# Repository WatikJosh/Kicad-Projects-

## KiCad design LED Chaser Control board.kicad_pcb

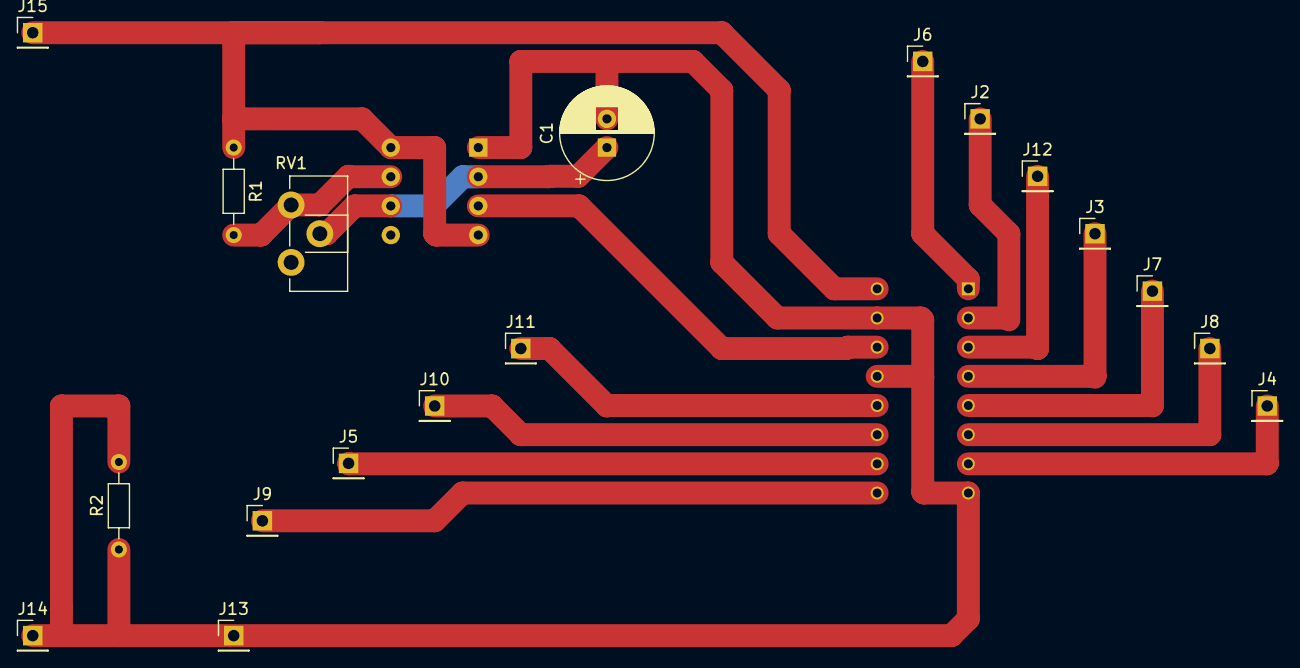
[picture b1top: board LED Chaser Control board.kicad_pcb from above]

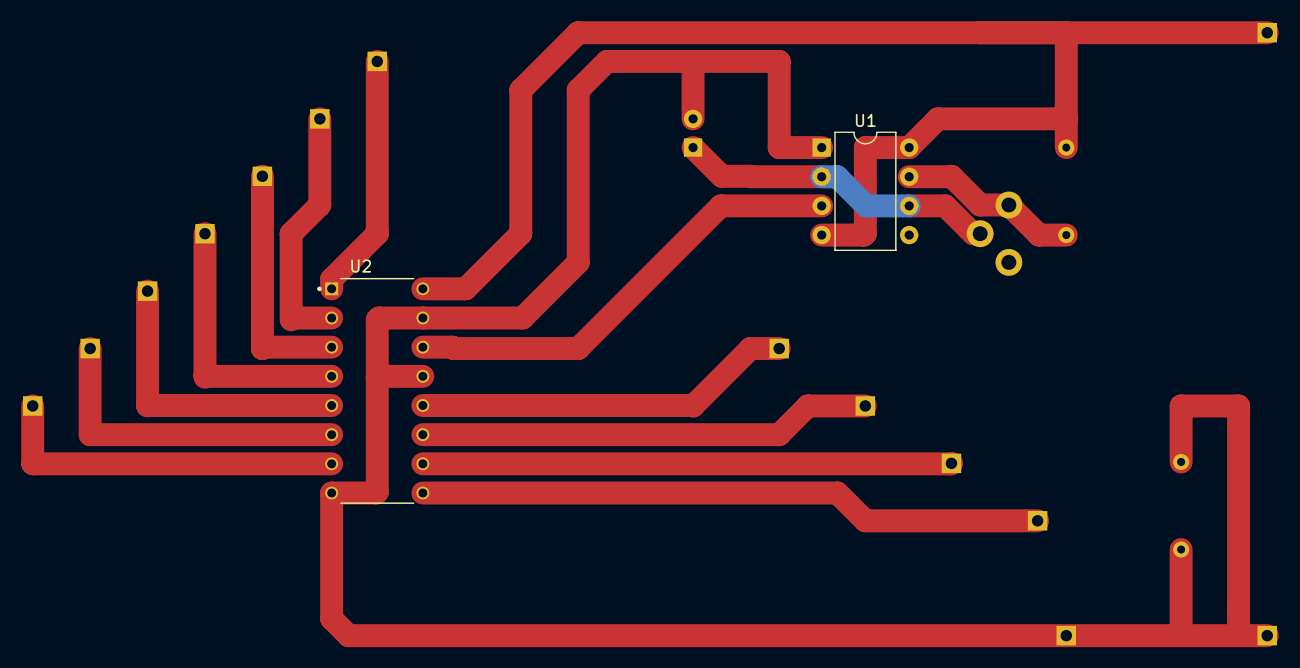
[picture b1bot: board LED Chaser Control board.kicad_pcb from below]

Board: 2 copper layers, 20 parts (2 on the bottom side), 17 nets.

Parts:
C1: 2.2; CP_Radial_D8.0mm_P2.50mm
J2, J3, J4, J5, J6, J7, J8, J9, J10, J11, J12, J13: Screw_Terminal_01x01; PinHeader_1x01_P2.54mm_Vertical
J14: GND; PinHeader_1x01_P2.54mm_Vertical
J15: Vcc; PinHeader_1x01_P2.54mm_Vertical
R1, R2: 1k; R_Axial_DIN0204_L3.6mm_D1.6mm_P7.62mm_Horizontal
RV1: 10k; Potentiometer_ACP_CA9-H2,5_Horizontal
U1: NE555P; DIP-8_W7.62mm
U2: CD4017BE; DIP794W45P254L1969H508Q16

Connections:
unnamed: J2.1, U2.2 (1)
unnamed: J3.1, U2.4 (2)
unnamed: J4.1, U2.7 (3)
unnamed: J5.1, U2.10 (4)
unnamed: J6.1, U2.1 (5)
unnamed: J7.1, U2.5 (6)
unnamed: J8.1, U2.6 (7)
unnamed: J9.1, U2.9 (8)
unnamed: J10.1, U2.11 (9)
unnamed: J11.1, U2.12 (CARRY_OUT)
unnamed: J12.1, U2.3 (O)
unnamed: J13.1, R2.2
unnamed: C1.2, J14.1, R2.1, U1.1 (GND), U2.8 (VSS), U2.13 (CLOCK_INHIBIT), U2.15 (RESET)
unnamed: J15.1, R1.1, U1.4 (R), U1.8 (VCC), U2.16 (VDD)
unnamed: R1.2, RV1.1, U1.7 (DIS)
unnamed: U1.3 (Q), U2.14 (CLOCK)
unnamed: C1.1, RV1.2, U1.2 (TR), U1.6 (THR)

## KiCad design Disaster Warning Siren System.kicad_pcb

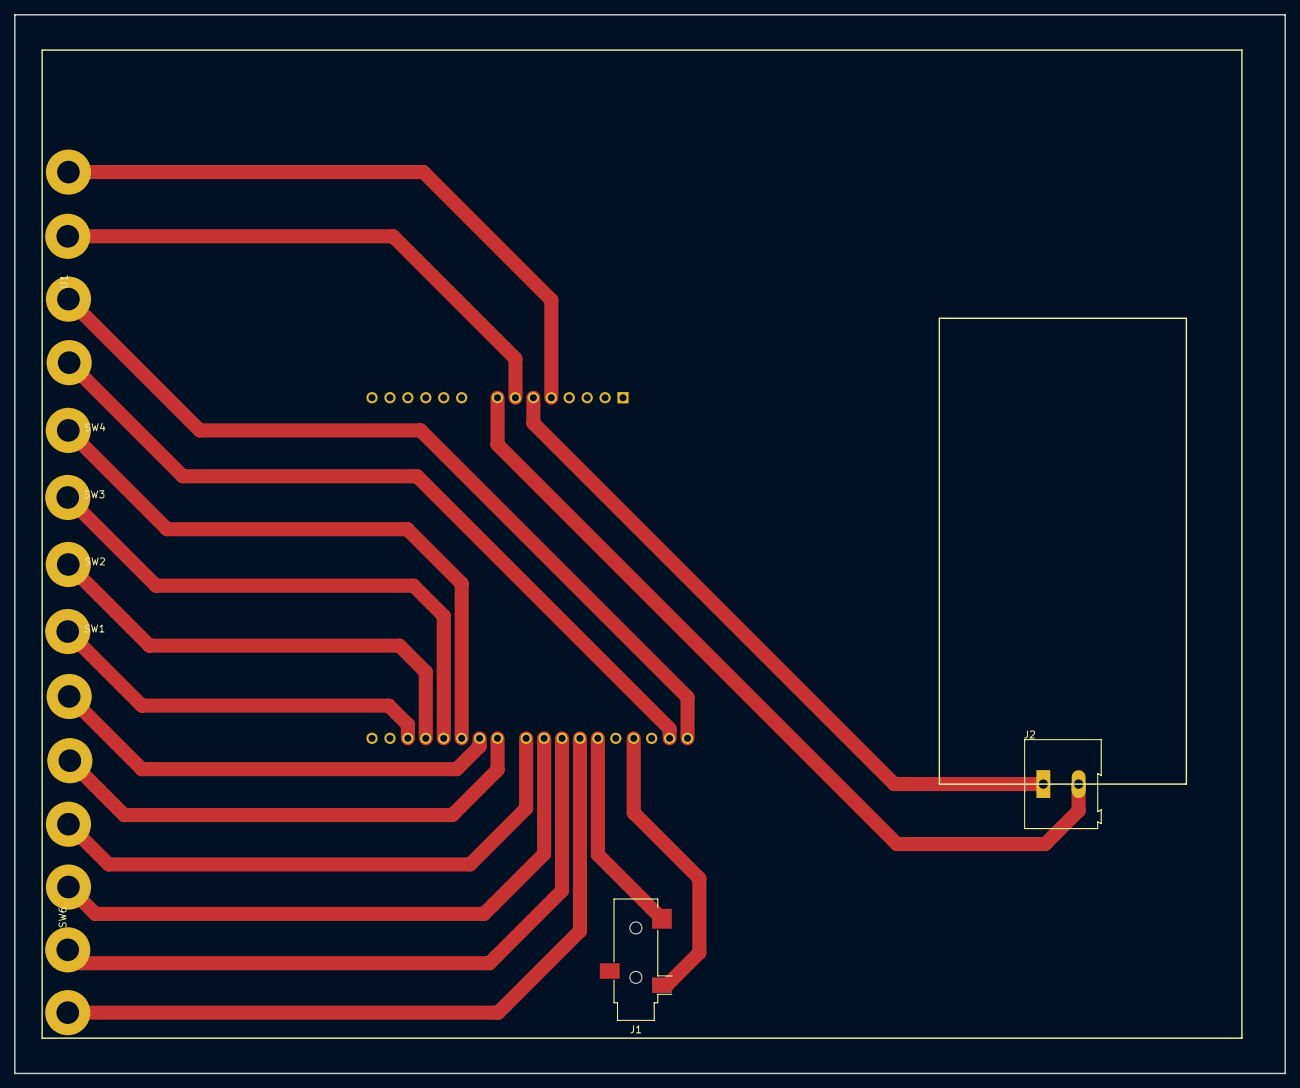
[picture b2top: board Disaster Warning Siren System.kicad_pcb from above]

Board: 2 copper layers, 180.0 x 150.0 mm, 9 parts (1 on the bottom side), 16 nets.

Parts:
A1: Arduino_UNO_R3
J1: AudioPlug2; Jack_3.5mm_CUI_SJ-3523-SMT_Horizontal
J2: Conn_01x02_Socket; TerminalBlock_Altech_AK300-2_P5.00mm
SW1: Sound 1; Button 3M
SW2: Sound 2; Button 3M
SW3: Sound 3; Button 3M
SW4: Mute; Button 3M
SW6: SW_Rotary_1x6_MP; Rotary Switch 3M
U1: LCD I2C Display; Rotary Switch 3M

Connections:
+5V_Arduino: A1.5 (+5V), U1.1 (GND)
GND: A1.6 (GND), A1.7 (GND), A1.29 (GND), J1.S, J2.1, U1.2 (VCC)
unnamed: A1.17 (D2), SW1.2
unnamed: A1.18 (D3), SW2.2
unnamed: A1.19 (D4), SW3.2
unnamed: A1.20 (D5), SW4.2
unnamed: A1.21 (D6), SW6.1
unnamed: A1.22 (D7), SW6.2
unnamed: A1.23 (D8), SW6.3
unnamed: A1.24 (D9), SW6.4
unnamed: A1.25 (D10), SW6.5
unnamed: A1.26 (D11), SW6.6
unnamed: A1.27 (D12), J1.T
unnamed: A1.8 (VIN), J2.2
unnamed: A1.32 (SCL/A5), U1.4 (SCL)
unnamed: A1.31 (SDA/A4), U1.3 (SDA)
